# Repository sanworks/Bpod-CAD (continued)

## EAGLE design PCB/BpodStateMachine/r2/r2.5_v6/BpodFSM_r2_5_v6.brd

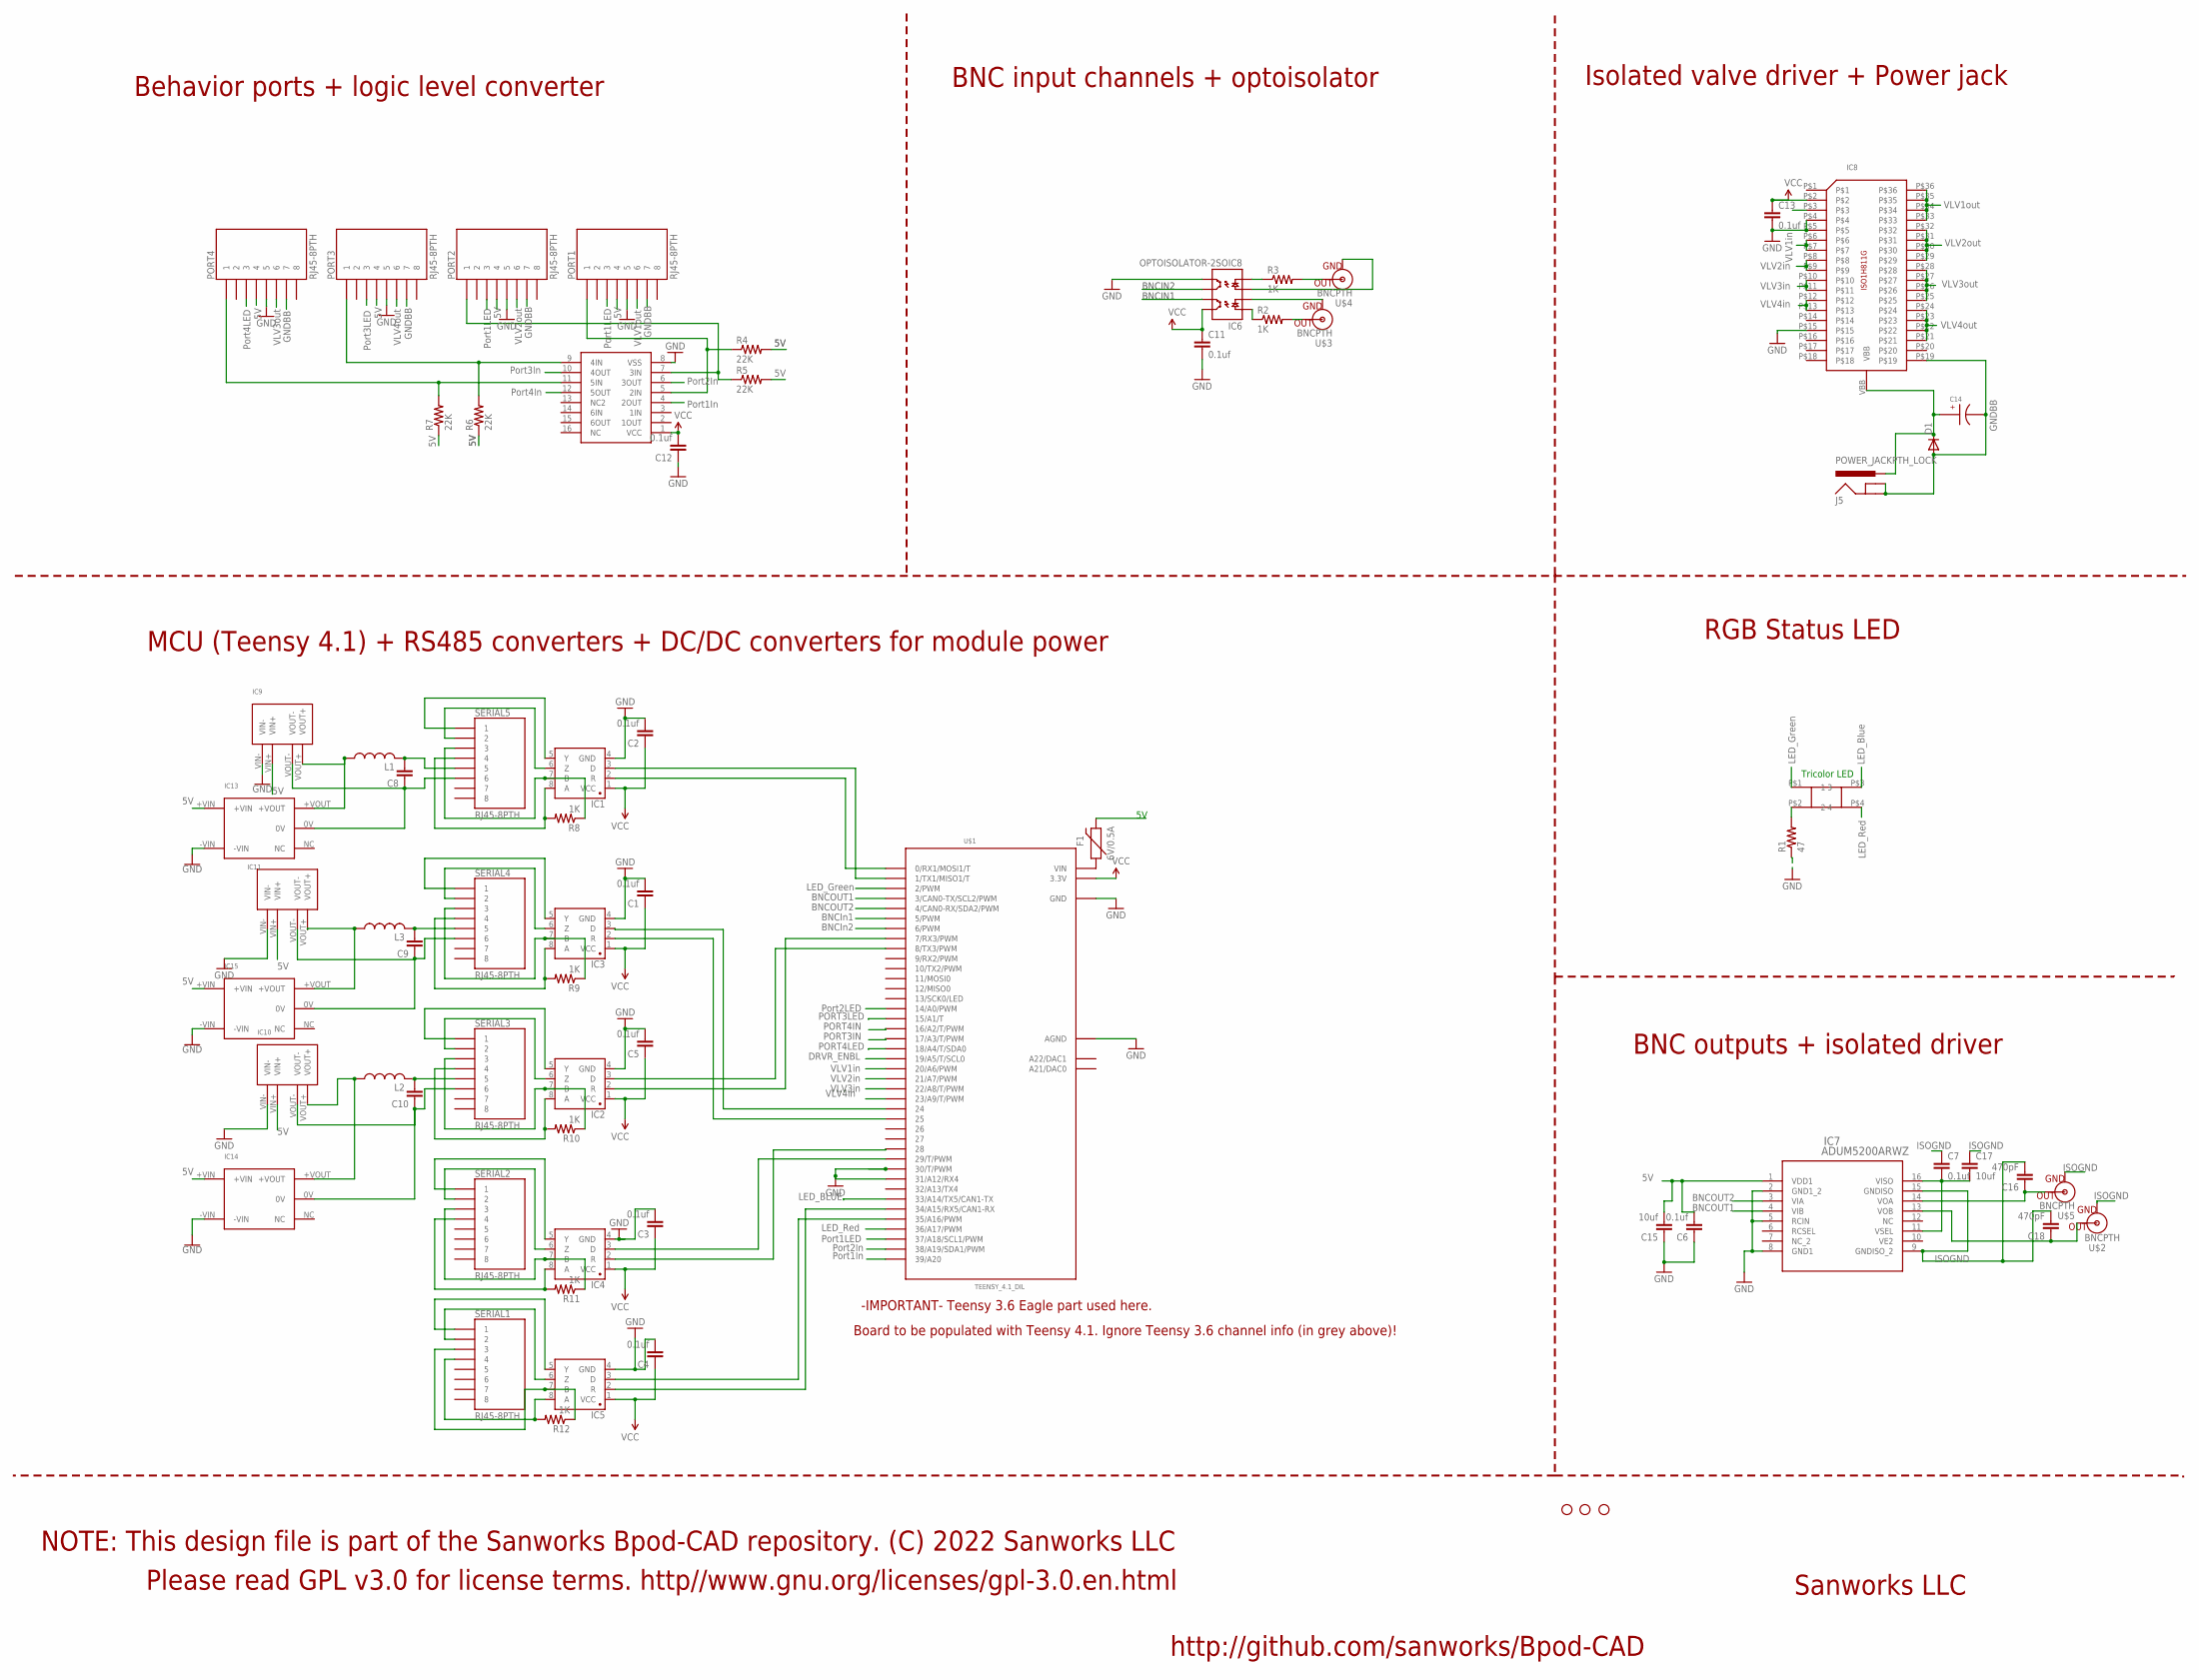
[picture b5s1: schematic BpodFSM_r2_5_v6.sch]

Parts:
C1, C2, C3, C4, C5, C11, C12, C13: 0.1uf; 1206@1
C6, C7: 0.1uf; 0805
C8, C9, C10: CAP1206; 1206@1
C14: EEE-FK1H100UR
C15, C17: 10uf; 1206@1
C16, C18: 470pF; 0805
D1: DIODE-DO214AA; DO214AA
F1: 6V/0.5A; 1206
IC1, IC2, IC3, IC4, IC5: SN65HVD31DR; SO08
IC6: OPTOISOLATOR-2SOIC8; SO08-2
IC7: ADUM5200ARWZ; RW_16
IC8: ISO1H811G
IC9, IC10, IC11: NME0509SC
IC12: CD4050; SO16
IC13, IC14, IC15: MTU1D0505MC
J5: POWER_JACKPTH_LOCK; POWER_JACK_PTH_LOCK
JP3, JP4, JP5: STAND-OFF
L1, L2, L3: L-USL3225M; L3225M
PORT1, PORT2, PORT3, PORT4: RJ45-8PTH; RJ45-8
R1: 47; 1206
R2, R3, R8, R9, R10, R11, R12: 1K; 1206
R4, R5, R6, R7: 22K; 1206
SERIAL1, SERIAL2, SERIAL3, SERIAL4, SERIAL5: RJ45-8PTH; RJ45-8
U$1: TEENSY_4.1_DIL; TEENSY_3.6_DIL
U$2, U$3, U$4, U$5: BNCPTH; BNC
U$8: SQUARE_TRICOLOR_LED

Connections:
5V: C6.2, C15.2, F1.2, IC7.1 (VDD1), IC9.VIN+, IC10.VIN+, IC11.VIN+, IC13.+VIN, IC14.+VIN, IC15.+VIN, PORT1.4, PORT2.4, PORT3.4, PORT4.4, R4.2, R5.2, R6.1, R7.1
BNCIN1: IC6.7 (EM1), U$1.6 (6/PWM)
BNCIN2: IC6.6 (CL2), U$1.5 (5/PWM)
BNCOUT1: IC7.4 (VIB), U$1.4 (4/CAN0-RX/SDA2/PWM)
BNCOUT2: IC7.3 (VIA), U$1.3 (3/CAN0-TX/SCL2/PWM)
DRVR_ENBL: IC8.P$3, U$1.19/A5 (19/A5/T/SCL0)
GND: C1.2, C2.2, C3.2, C4.2, C5.2, C6.1, C11.2, C12.1, C13.2, C15.1, IC1.4 (GND), IC2.4 (GND), IC3.4 (GND), IC4.4 (GND), IC5.4 (GND), IC6.5 (EM2), IC7.2 (GND1_2), IC7.5 (RCIN), IC7.8 (GND1), IC8.P$4, IC8.P$5, IC8.P$15, IC9.VIN-, IC10.VIN-, IC11.VIN-, IC12.8 (VSS), IC13.-VIN, IC14.-VIN, IC15.-VIN, PORT1.5, PORT2.5, PORT3.5, PORT4.5, R1.1, U$1.30 (30/T/PWM), U$1.31/A12 (31/A12/RX4), U$1.AGND, U$1.GND, U$1.GND1 (GND)
GNDBB: C14.CATHODE, D1.A, IC8.P$19, J5.GND, J5.GNDBREAK, PORT1.7, PORT2.7, PORT3.7, PORT4.7
ISOGND: C7.1, C16.2, C17.1, C18.2, IC7.9 (GNDISO_2), IC7.15 (GNDISO), U$2.GND, U$5.GND
LED_BLUE: U$1.33/A14 (33/A14/TX5/CAN1-TX), U$8.P$3 (3)
LED_GREEN: U$1.2 (2/PWM), U$8.P$1 (1)
LED_RED: U$1.36/A17 (36/A17/PWM), U$8.P$4 (4)
unnamed: IC3.8 (A), R9.2, SERIAL4.4
unnamed: IC3.7 (B), R9.1, SERIAL4.3
unnamed: IC3.6 (Z), SERIAL4.2
unnamed: IC3.5 (Y), SERIAL4.1
unnamed: IC3.2 (R), U$1.25
unnamed: IC3.3 (D), U$1.24
unnamed: IC1.8 (A), R8.2, SERIAL5.4
unnamed: IC1.7 (B), R8.1, SERIAL5.3
unnamed: IC1.6 (Z), SERIAL5.2
unnamed: IC1.5 (Y), SERIAL5.1
unnamed: IC1.2 (R), U$1.0 (0/RX1/MOSI1/T)
unnamed: IC1.3 (D), U$1.1 (1/TX1/MISO1/T)
unnamed: IC6.3 (A2), U$4.GND
unnamed: R3.2, U$4.S (OUT)
unnamed: R2.2, U$3.S (OUT)
unnamed: IC6.2 (C1), U$3.GND
unnamed: IC2.8 (A), R10.2, SERIAL3.4
unnamed: IC2.7 (B), R10.1, SERIAL3.3
unnamed: IC2.6 (Z), SERIAL3.2
unnamed: IC12.7 (3IN), PORT2.1, R5.1
unnamed: IC2.5 (Y), SERIAL3.1
unnamed: IC2.2 (R), U$1.7 (7/RX3/PWM)
unnamed: C8.2, L1.2, SERIAL5.5
unnamed: IC12.9 (4IN), PORT3.1, R6.2
unnamed: R1.2, U$8.P$2 (2)
unnamed: C8.1, IC9.VOUT-, IC13.0V, SERIAL5.6
unnamed: C18.1, IC7.13 (VOB), U$2.S (OUT)
unnamed: IC2.3 (D), U$1.8 (8/TX3/PWM)
unnamed: F1.1, U$1.VIN
unnamed: IC4.2 (R), U$1.28
unnamed: IC12.11 (5IN), PORT4.1, R7.2
unnamed: IC5.8 (A), R12.2, SERIAL1.4
unnamed: IC5.7 (B), R12.1, SERIAL1.3
unnamed: IC5.6 (Z), SERIAL1.2
unnamed: IC5.5 (Y), SERIAL1.1
unnamed: IC4.8 (A), R11.2, SERIAL2.4
unnamed: IC4.7 (B), R11.1, SERIAL2.3
unnamed: IC4.6 (Z), SERIAL2.2
unnamed: IC9.VOUT+, IC13.+VOUT, L1.1
unnamed: IC4.5 (Y), SERIAL2.1
unnamed: IC11.VOUT+, IC15.+VOUT, L3.1
unnamed: IC5.2 (R), U$1.34/A15 (34/A15/RX5/CAN1-RX)
unnamed: C10.1, IC10.VOUT-, IC14.0V, SERIAL3.6
unnamed: C10.2, L2.2, SERIAL3.5
unnamed: IC10.VOUT+, IC14.+VOUT, L2.1
unnamed: C7.2, C17.2, IC7.11 (VSEL), IC7.16 (VISO)
unnamed: C9.1, IC11.VOUT-, IC15.0V, SERIAL4.6
unnamed: IC5.3 (D), U$1.35/A16 (35/A16/PWM)
unnamed: C9.2, L3.2, SERIAL4.5
unnamed: C16.1, IC7.14 (VOA), U$5.S (OUT)
unnamed: IC4.3 (D), U$1.29 (29/T/PWM)
unnamed: IC6.1 (A1), R2.1
unnamed: IC6.4 (C2), R3.1
unnamed: IC12.5 (2IN), PORT1.1, R4.1
PORT1IN: IC12.4 (2OUT), U$1.39/A20
PORT1LED: PORT1.3, U$1.37/A18 (37/A18/SCL1/PWM)
PORT2IN: IC12.6 (3OUT), U$1.38/A19 (38/A19/SDA1/PWM)
PORT2LED: PORT2.3, U$1.14/A0 (14/A0/PWM)
PORT3IN: IC12.10 (4OUT), U$1.17/A3 (17/A3/T/PWM)
PORT3LED: PORT3.3, U$1.15/A1 (15/A1/T)
PORT4IN: IC12.12 (5OUT), U$1.16/A2 (16/A2/T/PWM)
PORT4LED: PORT4.3, U$1.18/A4 (18/A4/T/SDA0)
VBB: C14.ANODE, D1.C, IC8.VBB, J5.PWR
VCC: C1.1, C2.1, C3.1, C4.1, C5.1, C11.1, C12.2, C13.1, IC1.1 (VCC), IC2.1 (VCC), IC3.1 (VCC), IC4.1 (VCC), IC5.1 (VCC), IC6.8 (CL1), IC8.P$2, IC12.1 (VCC), U$1.3.3V, U$1.3.3V3 (3.3V)
VLV1IN: IC8.P$6, IC8.P$7, U$1.23/A9 (23/A9/T/PWM)
VLV1OUT: IC8.P$33, IC8.P$34, IC8.P$35, IC8.P$36, PORT1.6
VLV2IN: IC8.P$8, IC8.P$9, U$1.22/A8 (22/A8/T/PWM)
VLV2OUT: IC8.P$29, IC8.P$30, IC8.P$31, IC8.P$32, PORT2.6
VLV3IN: IC8.P$12, IC8.P$13, U$1.20/A6 (20/A6/PWM)
VLV3OUT: IC8.P$21, IC8.P$22, IC8.P$23, IC8.P$24, PORT3.6
VLV4IN: IC8.P$10, IC8.P$11, U$1.21/A7 (21/A7/PWM)
VLV4OUT: IC8.P$25, IC8.P$26, IC8.P$27, IC8.P$28, PORT4.6

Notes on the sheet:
Tricolor LED
LED_Blue
LED_Red
LED_Green
BNCIN1
BNCIN2
BNCIn1
BNCIn2
BNCOUT1
BNCOUT2
Port1In
Port2In
Port3In
Port4In
Port1LED
Port2LED
Port3LED
Port4LED
DRVR_ENBL
VLV2in
VLV3in
VLV4in
VLV1in
GNDBB
VLV1out
VLV2out
VLV3out
VLV4out
Sanworks LLC
http://github.com/sanworks/Bpod-CAD
Please read GPL v3.0 for license terms. http//www.gnu.org/licenses/gpl-3.0.en.html
NOTE: This design file is part of the Sanworks Bpod-CAD repository. (C) 2022 Sanworks LLC
Behavior ports + logic level converter
BNC input channels + optoisolator
Isolated valve driver + Power jack
RGB Status LED
BNC outputs + isolated driver
MCU (Teensy 4.1) + RS485 converters + DC/DC converters for module power
-IMPORTANT- Teensy 3.6 Eagle part used here.
Board to be populated with Teensy 4.1. Ignore Teensy 3.6 channel info (in grey above)!

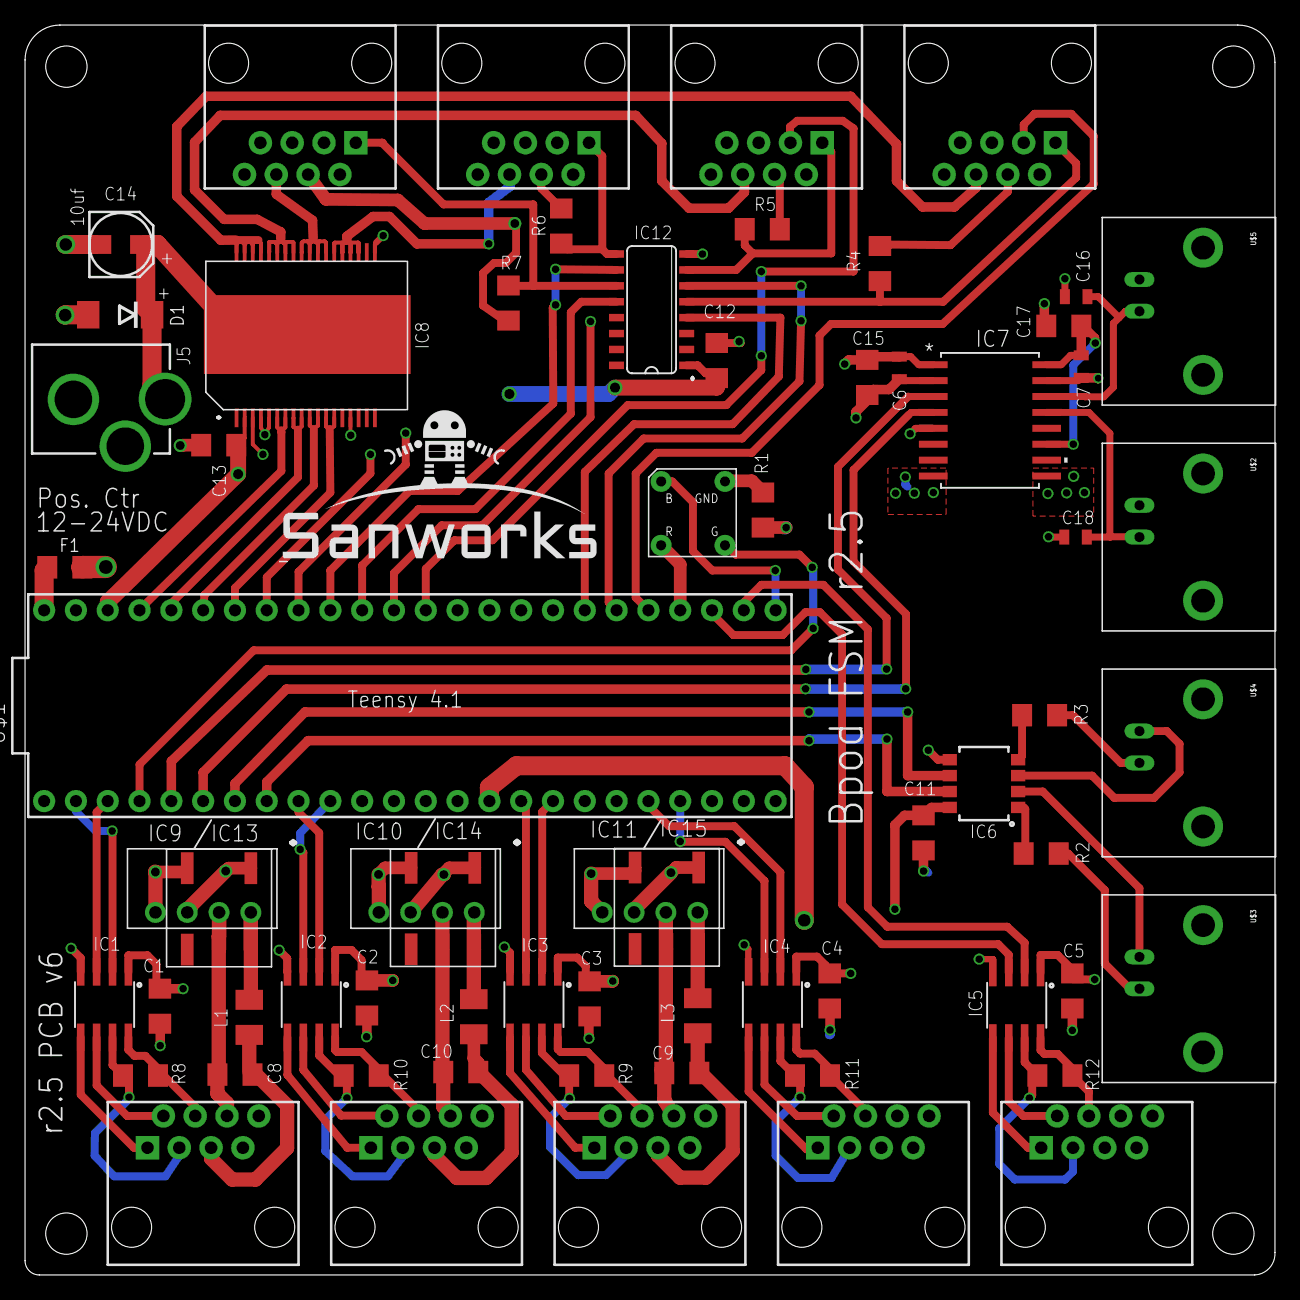
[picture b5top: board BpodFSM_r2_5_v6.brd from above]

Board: 4 copper layers, 99.8 x 99.8 mm, 71 parts (0 on the bottom side), 84 nets.

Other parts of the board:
JP1: STAND-OFF
U$6: SANWORKS_LOGO

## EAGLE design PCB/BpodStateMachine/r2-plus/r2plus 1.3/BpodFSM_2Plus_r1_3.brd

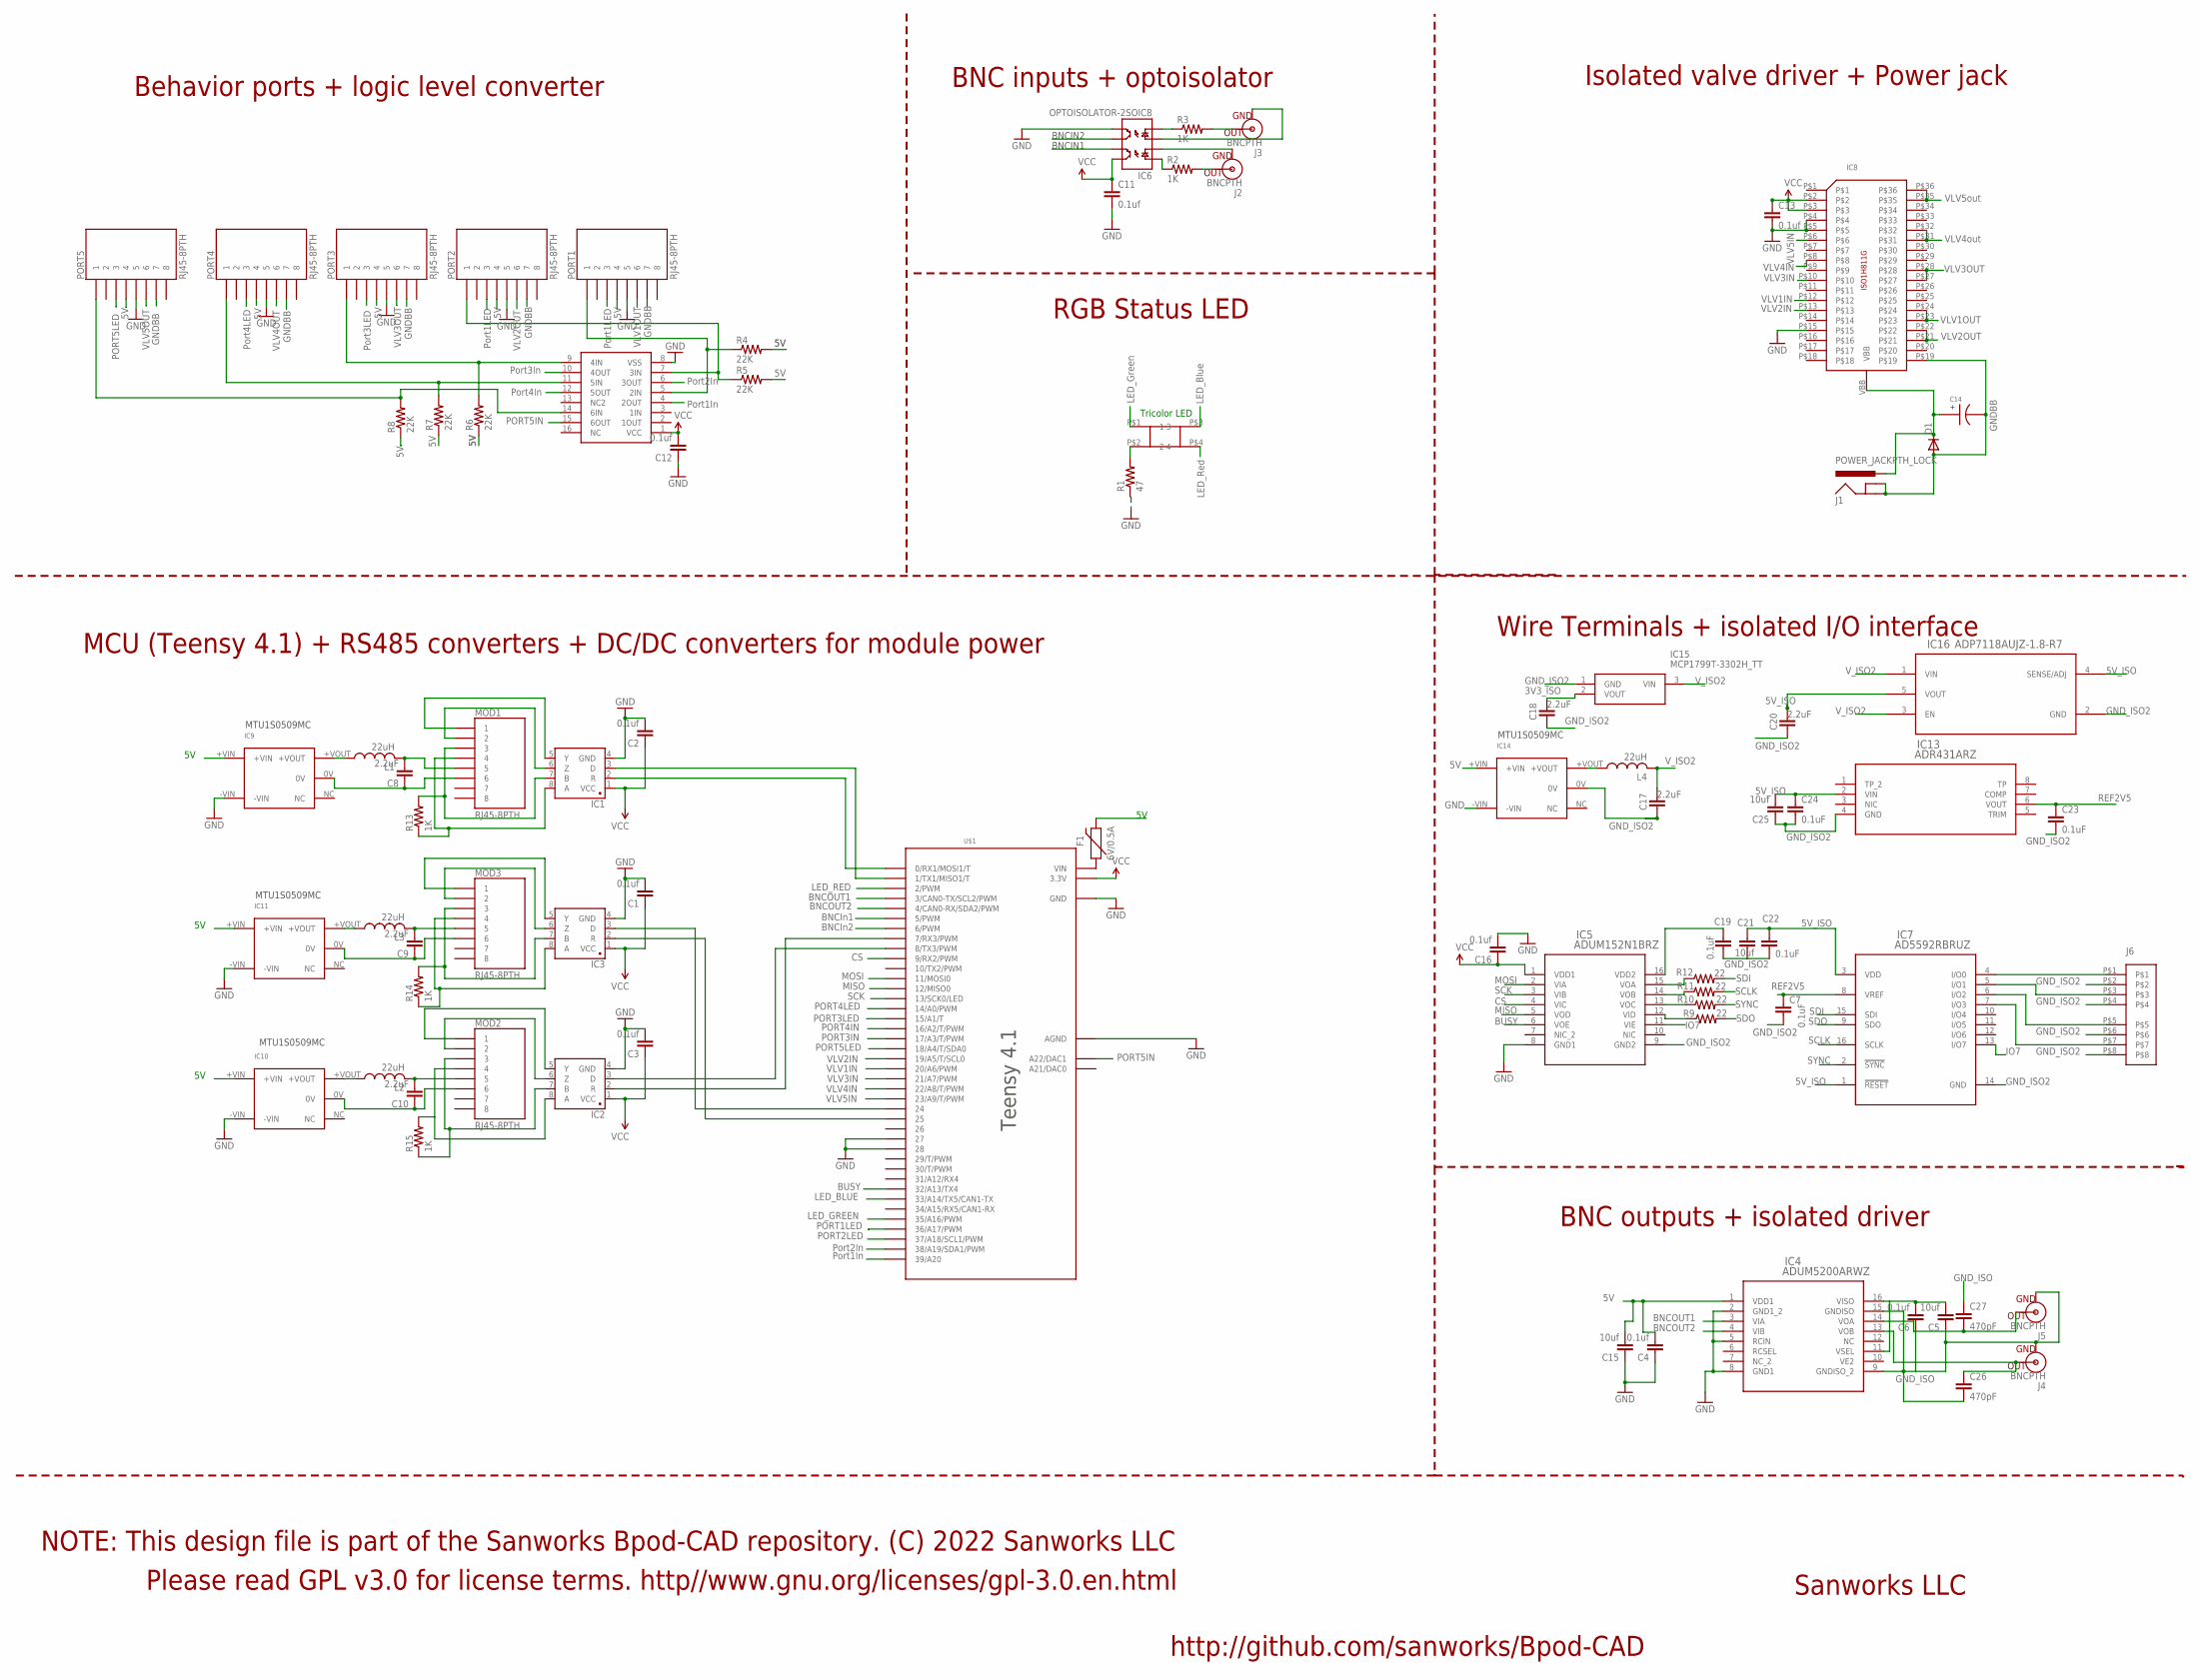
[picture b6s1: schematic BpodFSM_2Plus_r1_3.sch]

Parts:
C1, C2, C3, C4, C6, C11, C12, C13, C16: 0.1uf; 0805
C5, C15, C21, C25: 10uf; 1206@1
C7, C19, C22, C23, C24: 0.1uF; 0805
C8, C9, C10, C17, C18, C20: 2.2uF; 0805
C14: EEE-FK1H100UR
C26, C27: 470pF; 0805
D1: DIODE-DO214AA; DO214AA
F1: 6V/0.5A; 1206
IC1, IC2, IC3: SN65HVD31DR; SO08
IC4: ADUM5200ARWZ; RW_16
IC5: ADUM152N1BRZ; R-16_ADI
IC6: OPTOISOLATOR-2SOIC8; SO08-2
IC7: AD5592RBRUZ; RU_16_ADI
IC8: ISO1H811G
IC9, IC10, IC11: 9V; MTU1D0505MC
IC12: CD4050; SO16
IC13: ADR431ARZ; R_8_ADI
IC14: 5V; MTU1D0505MC
IC15: MCP1799T-3302H_TT; SOT95P237X112-3N
IC16: ADP7118AUJZ-1.8-R7; UJ_5
J1: POWER_JACKPTH_LOCK; POWER_JACK_PTH_LOCK
J2, J3, J4, J5: BNCPTH; BNC
J6: 8POS_MOLEX_SOCKET
L1, L2, L3, L4: 22uH; L3225M
MOD1, MOD2, MOD3: RJ45-8PTH; RJ45-8
PORT1, PORT2, PORT3, PORT4, PORT5: RJ45-8PTH; RJ45-8
R1: 47; 1206
R2, R3, R13, R14, R15: 1K; 1206
R4, R5, R6, R7, R8: 22K; 1206
R9, R10, R11, R12: 22; R0805
U$1: TEENSY_3.6_DIL
U$8: SQUARE_TRICOLOR_LED

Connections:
3V3_ISO: C18.2, C19.1, IC5.16 (VDD2), IC15.2 (VOUT)
5V: C4.2, C15.2, F1.2, IC4.1 (VDD1), IC9.+VIN, IC10.+VIN, IC11.+VIN, IC14.+VIN, PORT1.4, PORT2.4, PORT3.4, PORT4.4, PORT5.4, R4.2, R5.2, R6.1, R7.1, R8.1
5V_ISO: C20.2, C21.2, C22.1, C24.1, C25.2, IC7.1 (!RESET), IC7.3 (VDD), IC13.2 (VIN), IC16.4 (SENSE/ADJ), IC16.5 (VOUT)
BNCIN1: IC6.7 (EM1), U$1.6 (6/PWM)
BNCIN2: IC6.6 (CL2), U$1.5 (5/PWM)
BNCOUT1: IC4.3 (VIA), U$1.3 (3/CAN0-TX/SCL2/PWM)
BNCOUT2: IC4.4 (VIB), U$1.4 (4/CAN0-RX/SDA2/PWM)
BUSY: IC5.6 (VOE), U$1.32/A13 (32/A13/TX4)
CS: IC5.4 (VIC), U$1.9 (9/RX2/PWM)
GND: C1.2, C2.2, C3.2, C4.1, C11.2, C12.1, C13.2, C15.1, C16.2, IC1.4 (GND), IC2.4 (GND), IC3.4 (GND), IC4.2 (GND1_2), IC4.5 (RCIN), IC4.8 (GND1), IC5.8 (GND1), IC6.5 (EM2), IC8.P$4, IC8.P$5, IC8.P$15, IC9.-VIN, IC10.-VIN, IC11.-VIN, IC12.8 (VSS), IC14.-VIN, PORT1.5, PORT2.5, PORT3.5, PORT4.5, PORT5.5, R1.1, U$1.27, U$1.28, U$1.AGND, U$1.GND, U$1.GND1 (GND)
GNDBB: C14.CATHODE, D1.A, IC8.P$19, J1.GND, J1.GNDBREAK, PORT1.7, PORT2.7, PORT3.7, PORT4.7, PORT5.7
GND_ISO: C5.1, C6.1, C26.2, C27.1, IC4.9 (GNDISO_2), IC4.15 (GNDISO), J4.GND, J5.GND
GND_ISO2: C7.2, C17.1, C18.1, C19.2, C20.1, C21.1, C22.2, C23.2, C24.2, C25.1, IC5.9 (GND2), IC7.14 (GND), IC13.4 (GND), IC14.0V, IC15.1 (GND), IC16.2 (GND), J6.P$2, J6.P$4, J6.P$6, J6.P$8
IO7: IC5.11 (VIE), IC7.13 (I/O7)
LED_BLUE: U$1.33/A14 (33/A14/TX5/CAN1-TX), U$8.P$3 (3)
LED_GREEN: U$1.35/A16 (35/A16/PWM), U$8.P$1 (1)
LED_RED: U$1.2 (2/PWM), U$8.P$4 (4)
MISO: IC5.5 (VOD), U$1.12 (12/MISO0)
MOSI: IC5.2 (VIA), U$1.11 (11/MOSI0)
unnamed: IC3.8 (A), MOD3.4, R14.1
unnamed: IC3.7 (B), MOD3.3, R14.2
unnamed: IC3.6 (Z), MOD3.2
unnamed: IC3.5 (Y), MOD3.1
unnamed: IC3.2 (R), U$1.25
unnamed: IC3.3 (D), U$1.24
unnamed: IC1.8 (A), MOD1.4, R13.1
unnamed: IC1.7 (B), MOD1.3, R13.2
unnamed: IC1.6 (Z), MOD1.2
unnamed: IC1.5 (Y), MOD1.1
unnamed: IC1.2 (R), U$1.0 (0/RX1/MOSI1/T)
unnamed: IC1.3 (D), U$1.1 (1/TX1/MISO1/T)
unnamed: IC6.3 (A2), J3.GND
unnamed: J3.S (OUT), R3.2
unnamed: J2.S (OUT), R2.2
unnamed: IC6.2 (C1), J2.GND
unnamed: IC2.8 (A), MOD2.4, R15.2
unnamed: IC2.7 (B), MOD2.3, R15.1
unnamed: IC2.6 (Z), MOD2.2
unnamed: IC12.7 (3IN), PORT2.1, R5.1
unnamed: IC2.5 (Y), MOD2.1
unnamed: IC2.2 (R), U$1.7 (7/RX3/PWM)
unnamed: C8.2, L1.2, MOD1.5
unnamed: IC12.9 (4IN), PORT3.1, R6.2
unnamed: R1.2, U$8.P$2 (2)
unnamed: C8.1, IC9.0V, MOD1.6
unnamed: C5.2, C6.2, IC4.11 (VSEL), IC4.16 (VISO)
unnamed: IC2.3 (D), U$1.8 (8/TX3/PWM)
unnamed: F1.1, U$1.VIN
unnamed: IC7.4 (I/O0), J6.P$1
unnamed: IC12.11 (5IN), PORT4.1, R7.2
unnamed: C27.2, IC4.14 (VOA), J5.S (OUT)
unnamed: C26.1, IC4.13 (VOB), J4.S (OUT)
unnamed: IC7.5 (I/O1), J6.P$3
unnamed: IC7.6 (I/O2), J6.P$5
unnamed: IC7.7 (I/O3), J6.P$7
unnamed: IC14.+VOUT, L4.1
unnamed: IC5.15 (VOA), R12.1
unnamed: IC9.+VOUT, L1.1
unnamed: IC5.14 (VOB), R11.1
unnamed: IC12.14 (6IN), PORT5.1, R8.2
unnamed: IC5.13 (VOC), R10.1
unnamed: C10.1, IC10.0V, MOD2.6
unnamed: C10.2, L2.2, MOD2.5
unnamed: IC10.+VOUT, L2.1
unnamed: IC5.12 (VID), R9.1
unnamed: C9.1, IC11.0V, MOD3.6
unnamed: C9.2, L3.2, MOD3.5
unnamed: IC11.+VOUT, L3.1
unnamed: IC6.1 (A1), R2.1
unnamed: IC6.4 (C2), R3.1
unnamed: IC12.5 (2IN), PORT1.1, R4.1
PORT1IN: IC12.4 (2OUT), U$1.39/A20
PORT1LED: PORT1.3, U$1.36/A17 (36/A17/PWM)
PORT2IN: IC12.6 (3OUT), U$1.38/A19 (38/A19/SDA1/PWM)
PORT2LED: PORT2.3, U$1.37/A18 (37/A18/SCL1/PWM)
PORT3IN: IC12.10 (4OUT), U$1.17/A3 (17/A3/T/PWM)
PORT3LED: PORT3.3, U$1.15/A1 (15/A1/T)
PORT4IN: IC12.12 (5OUT), U$1.16/A2 (16/A2/T/PWM)
PORT4LED: PORT4.3, U$1.14/A0 (14/A0/PWM)
PORT5IN: IC12.15 (6OUT), U$1.A22 (A22/DAC1)
PORT5LED: PORT5.3, U$1.18/A4 (18/A4/T/SDA0)
REF2V5: C7.1, C23.1, IC7.8 (VREF), IC13.6 (VOUT)
SCK: IC5.3 (VIB), U$1.13 (13/SCK0/LED)
SCLK: IC7.16 (SCLK), R11.2
SDI: IC7.15 (SDI), R12.2
SDO: IC7.9 (SDO), R9.2
SYNC: IC7.2 (!SYNC), R10.2
VBB: C14.ANODE, D1.C, IC8.VBB, J1.PWR
VCC: C1.1, C2.1, C3.1, C11.1, C12.2, C13.1, C16.1, IC1.1 (VCC), IC2.1 (VCC), IC3.1 (VCC), IC5.1 (VDD1), IC6.8 (CL1), IC8.P$2, IC8.P$3, IC12.1 (VCC), U$1.3.3V, U$1.3.3V3 (3.3V)
VLV1IN: IC8.P$12, U$1.20/A6 (20/A6/PWM)
VLV1OUT: IC8.P$23, IC8.P$24, PORT1.6
VLV2IN: IC8.P$13, U$1.19/A5 (19/A5/T/SCL0)
VLV2OUT: IC8.P$21, IC8.P$22, PORT2.6
VLV3IN: IC8.P$10, U$1.21/A7 (21/A7/PWM)
VLV3OUT: IC8.P$27, IC8.P$28, PORT3.6
VLV4IN: IC8.P$8, U$1.22/A8 (22/A8/T/PWM)
VLV4OUT: IC8.P$31, IC8.P$32, PORT4.6
VLV5IN: IC8.P$6, U$1.23/A9 (23/A9/T/PWM)
VLV5OUT: IC8.P$35, IC8.P$36, PORT5.6
V_ISO2: C17.2, IC15.3 (VIN), IC16.1 (VIN), IC16.3 (EN), L4.2

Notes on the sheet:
Tricolor LED
LED_Blue
LED_Red
LED_Green
BNCIN1
BNCIN2
BNCIn1
BNCIn2
Port1In
Port2In
Port3In
Port4In
Port1LED
Port3LED
Port4LED
GNDBB
VLV5out
VLV4out
Sanworks LLC
http://github.com/sanworks/Bpod-CAD
Please read GPL v3.0 for license terms. http//www.gnu.org/licenses/gpl-3.0.en.html
NOTE: This design file is part of the Sanworks Bpod-CAD repository. (C) 2022 Sanworks LLC
Behavior ports + logic level converter
BNC inputs + optoisolator
Isolated valve driver + Power jack
RGB Status LED
BNC outputs + isolated driver
MCU (Teensy 4.1) + RS485 converters + DC/DC converters for module power
Wire Terminals + isolated I/O interface
MTU1S0509MC
Teensy 4.1

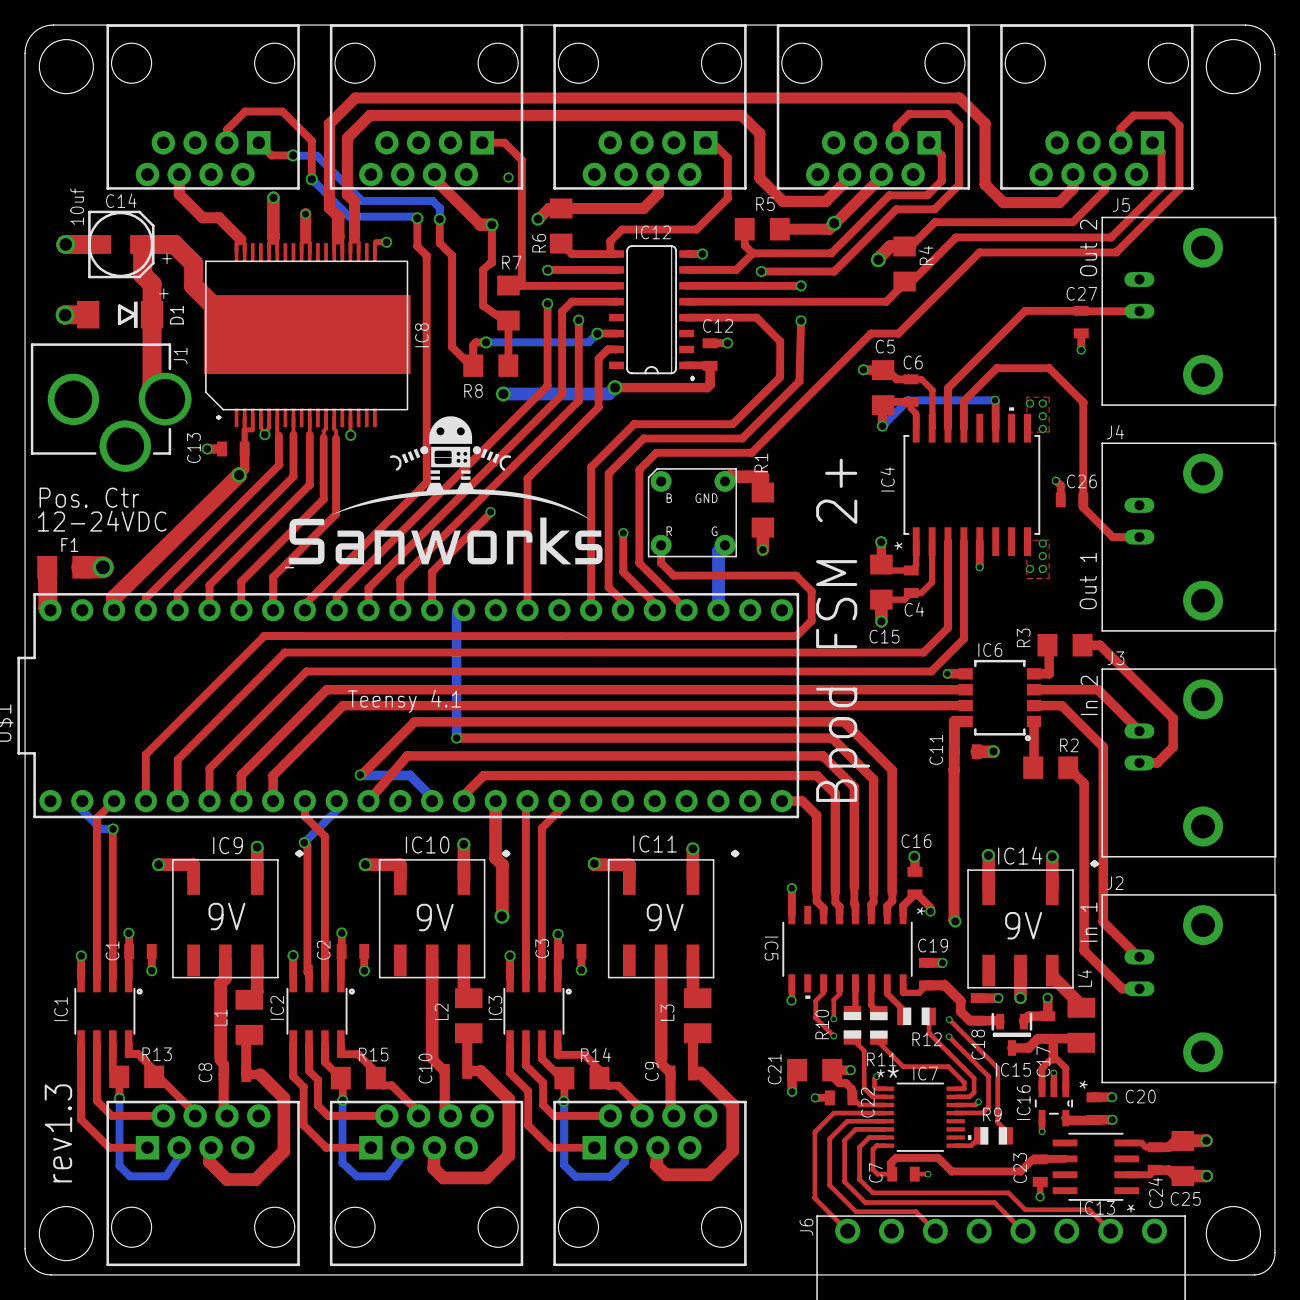
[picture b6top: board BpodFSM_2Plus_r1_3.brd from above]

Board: 4 copper layers, 99.8 x 99.8 mm, 81 parts (0 on the bottom side), 100 nets.

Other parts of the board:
U$7: SANWORKS_LOGO

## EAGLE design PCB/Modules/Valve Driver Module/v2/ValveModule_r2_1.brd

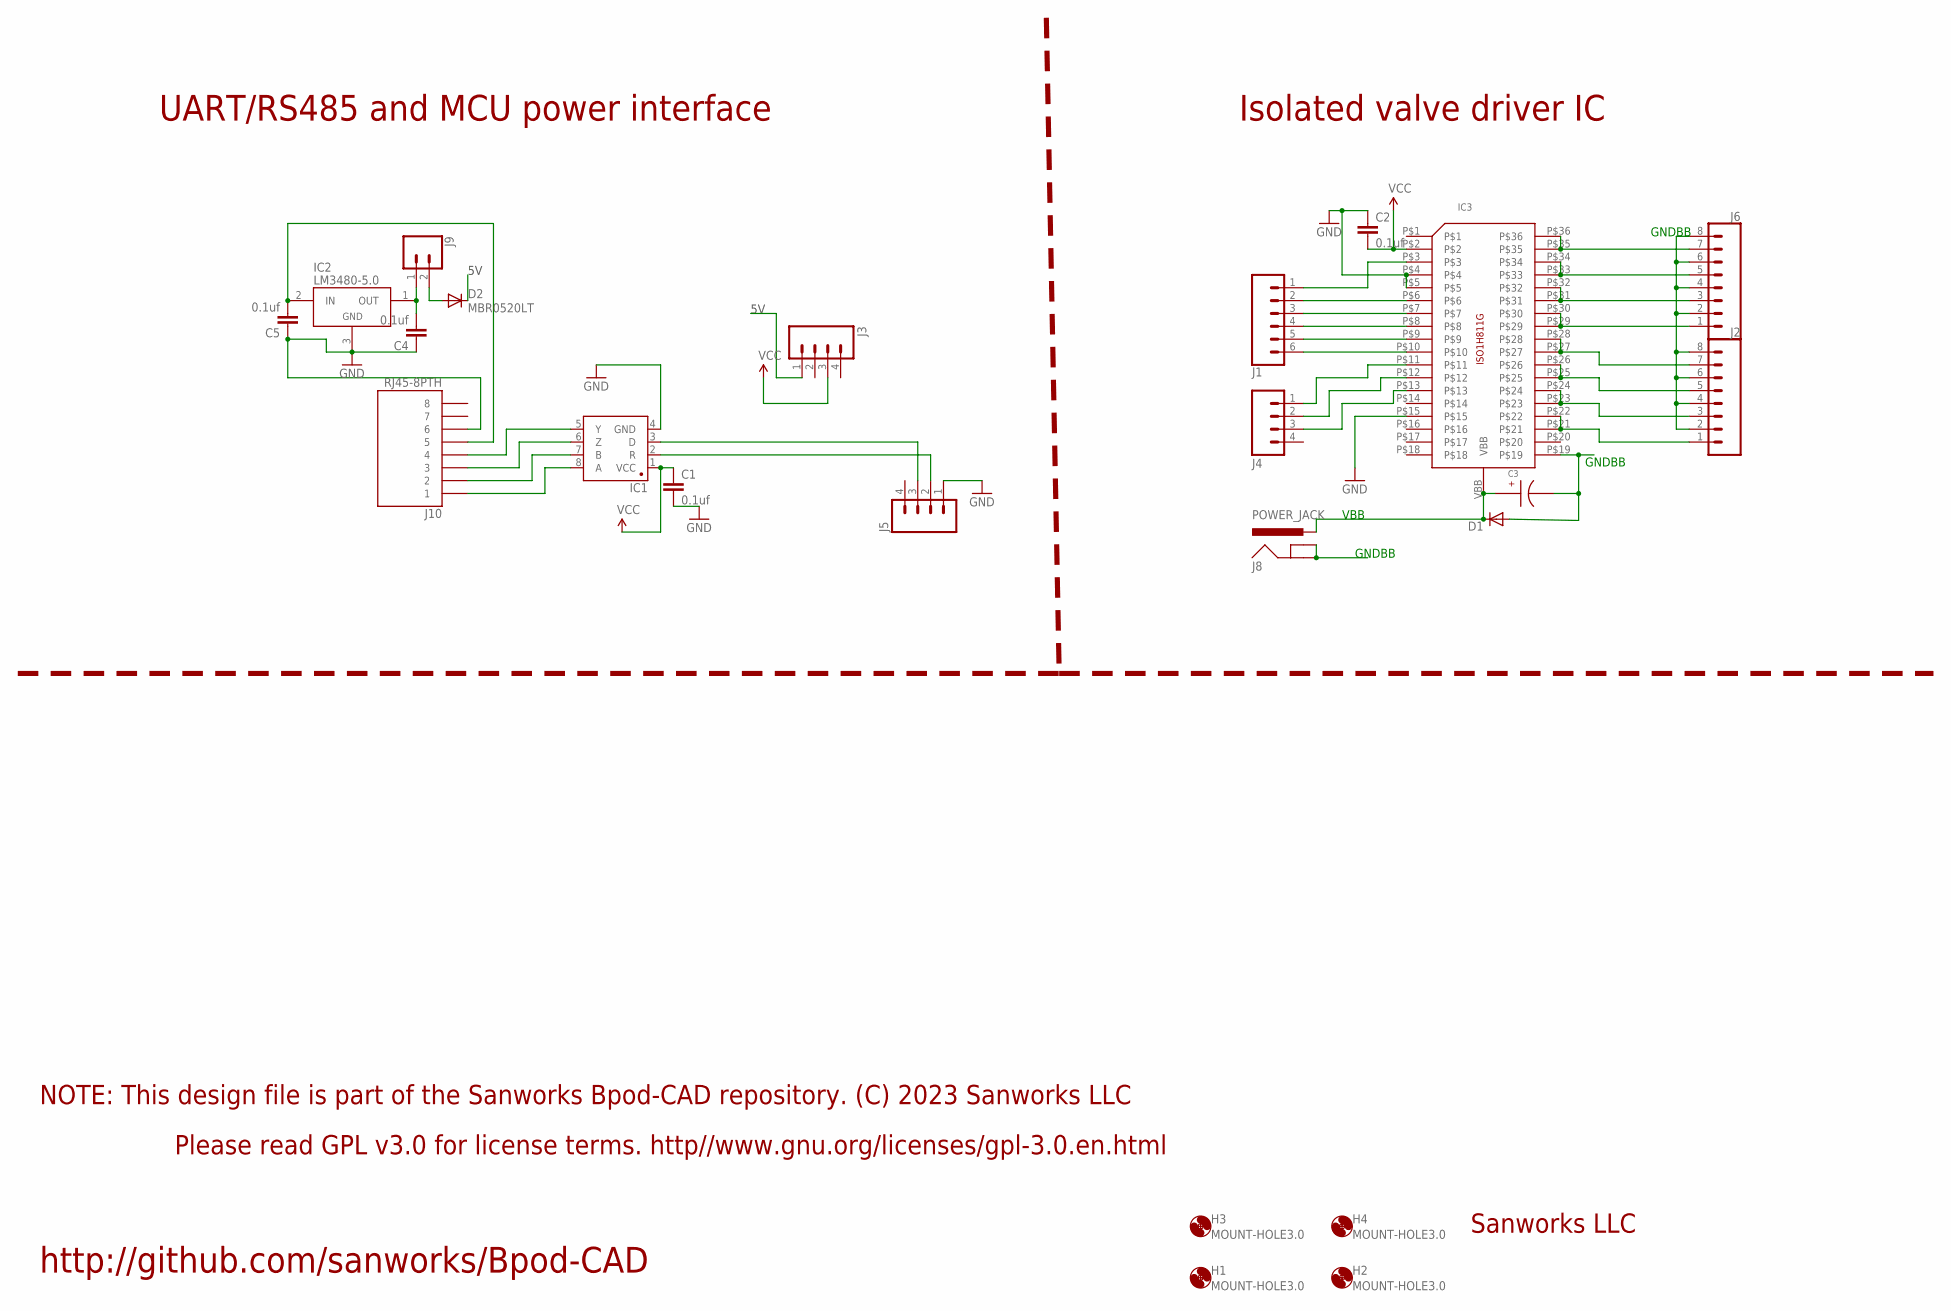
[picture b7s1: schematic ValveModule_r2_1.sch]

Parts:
C1, C2, C4, C5: 0.1uf; 1206
C3: EEE-FK1H100UR
D1: DIODE-DO214AA; DO214AA
D2: MBR0520LT; SOD123
H1, H2, H3, H4: MOUNT-HOLE3.0; 3,0
IC1: SN65HVD31DR; SO08
IC2: LM3480-5.0; SOT-23-3
IC3: ISO1H811G
J1: CONN_06SILK_FEMALE_PTH; 1X06
J2, J6: CONN_083.5MM-8; SCREWTERMINAL-3.5MM-8
J3, J4, J5: M04PTH; 1X04
J8: POWER_JACK; POWER_JACK_PTH
J9: CONN_02; 1X02
J10: RJ45-8PTH; RJ45-8

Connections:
5V: D2.C, J3.1
GND: C1.2, C2.1, C4.1, C5.1, IC1.4 (GND), IC2.3 (GND), IC3.P$4, IC3.P$5, IC3.P$15, J5.1, J10.6
GNDBB: C3.CATHODE, D1.A, IC3.P$19, J2.2, J2.4, J2.6, J2.8, J6.2, J6.4, J6.6, J6.8, J8.GND, J8.GNDBREAK
unnamed: IC3.P$35, IC3.P$36, J6.7
unnamed: IC3.P$3, J1.1
unnamed: IC3.P$6, J1.2
unnamed: IC1.3 (D), J5.3
unnamed: IC3.P$7, J1.3
unnamed: IC1.2 (R), J5.2
unnamed: IC1.8 (A), J10.1
unnamed: IC1.7 (B), J10.2
unnamed: IC1.6 (Z), J10.3
unnamed: IC1.5 (Y), J10.4
unnamed: IC3.P$8, J1.4
unnamed: IC3.P$9, J1.5
unnamed: IC3.P$10, J1.6
unnamed: IC3.P$11, J4.1
unnamed: IC3.P$12, J4.2
unnamed: IC3.P$13, J4.3
unnamed: IC3.P$33, IC3.P$34, J6.5
unnamed: IC3.P$31, IC3.P$32, J6.3
unnamed: IC3.P$29, IC3.P$30, J6.1
unnamed: IC3.P$27, IC3.P$28, J2.7
unnamed: IC3.P$25, IC3.P$26, J2.5
unnamed: IC3.P$23, IC3.P$24, J2.3
unnamed: IC3.P$21, IC3.P$22, J2.1
unnamed: C5.2, IC2.2 (IN), J10.5
unnamed: C4.2, IC2.1 (OUT), J9.1
unnamed: D2.A, J9.2
VBB: C3.ANODE, D1.C, IC3.VBB, J8.PWR
VCC: C1.1, C2.2, IC1.1 (VCC), IC3.P$2, J3.3

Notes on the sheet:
VBB
GNDBB
UART/RS485 and MCU power interface
Isolated valve driver IC
Please read GPL v3.0 for license terms. http//www.gnu.org/licenses/gpl-3.0.en.html
NOTE: This design file is part of the Sanworks Bpod-CAD repository. (C) 2023 Sanworks LLC
Sanworks LLC
http://github.com/sanworks/Bpod-CAD

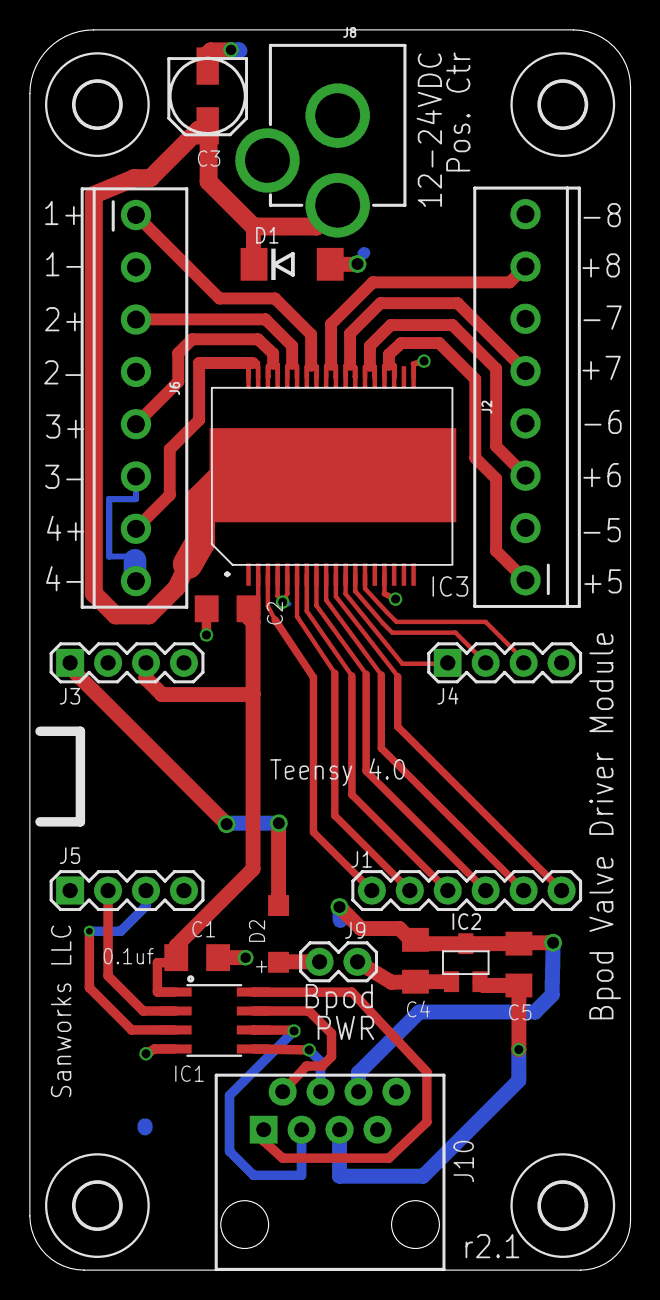
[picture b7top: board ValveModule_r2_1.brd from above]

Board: 2 copper layers, 40.2 x 83.0 mm, 23 parts (0 on the bottom side), 31 nets.
